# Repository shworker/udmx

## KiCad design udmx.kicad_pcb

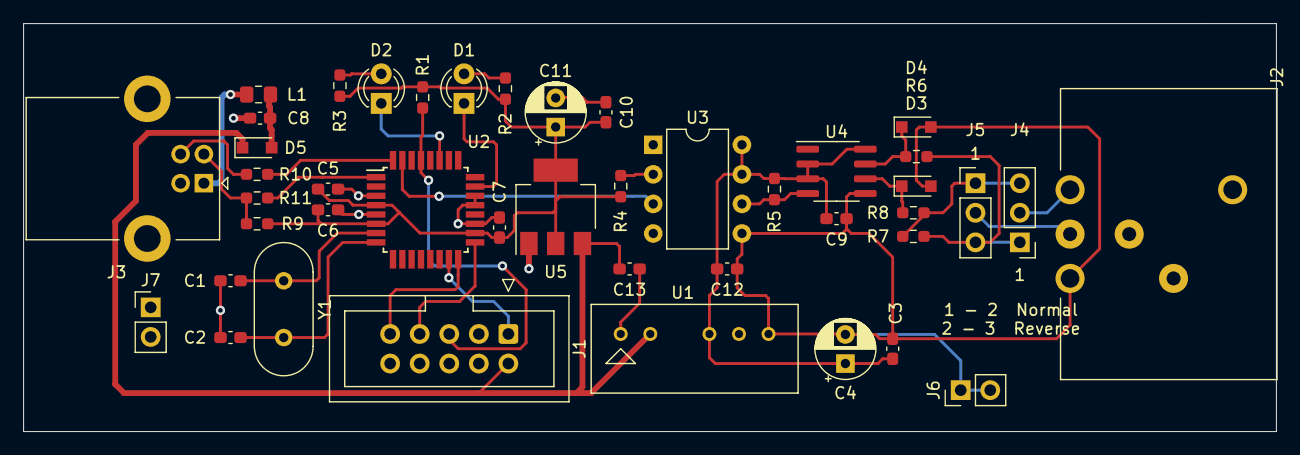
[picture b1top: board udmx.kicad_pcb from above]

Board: 2 copper layers, 107.6 x 35.1 mm, 43 parts (0 on the bottom side), 30 nets.

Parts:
C1, C2: 16pF; C_0603_1608Metric_Pad1.08x0.95mm_HandSolder
C3, C5, C6, C7, C8, C9, C10, C12, C13: 100n; C_0603_1608Metric_Pad1.08x0.95mm_HandSolder
C4, C11: 4.7uF; CP_Radial_D5.0mm_P2.50mm
D1, D2: LED; LED_D3.0mm
D3, D4: BZX384; D_SOD-323_HandSoldering
D5: BAT20J; D_SOD-323_HandSoldering
J1: AVR-ISP-10; IDC-Header_2x05_P2.54mm_Vertical
J2: XLR3; NC3MAH
J3: USB_B; USB_B_Lumberg_2411_02_Horizontal
J4, J5: Conn_01x03_Male; PinHeader_1x03_P2.54mm_Vertical
J6: GND_ISO; PinHeader_1x02_P2.54mm_Vertical
J7: GND; PinHeader_1x02_P2.54mm_Vertical
L1: 600R; L_0805_2012Metric_Pad1.15x1.40mm_HandSolder
R1: 10k; R_0603_1608Metric_Pad0.98x0.95mm_HandSolder
R2, R3: 300R; R_0603_1608Metric_Pad0.98x0.95mm_HandSolder
R4: 100R; R_0603_1608Metric_Pad0.98x0.95mm_HandSolder
R5: 1k; R_0603_1608Metric_Pad0.98x0.95mm_HandSolder
R6, R8: 22R; R_0603_1608Metric_Pad0.98x0.95mm_HandSolder
R7: 120R; R_0603_1608Metric_Pad0.98x0.95mm_HandSolder
R9: 1,5k; R_0603_1608Metric_Pad0.98x0.95mm_HandSolder
R10, R11: 68R; R_0603_1608Metric_Pad0.98x0.95mm_HandSolder
U1: TMR1-0511; SIP-6
U2: ATmega8-16AU; TQFP-32_7x7mm_P0.8mm
U3: 6N137; DIP-8_W7.62mm
U4: MAX485E; SOIC-8_3.9x4.9mm_P1.27mm
U5: LM1117-3.3; SOT-223-3_TabPin2
Y1: 12 MHz; Crystal_HC49-4H_Vertical

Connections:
+3V3: C5.1, C6.1, C7.1, C10.1, C11.1, R1.1, R2.1, R3.1, R4.2, R9.1, U2.4, U2.6, U2.18, U5.2
+5V: C13.1, D5.1, J1.2, U1.2, U5.3
/5VISO+: C3.1, C4.1, C9.1, C12.1, R5.1, U1.4, U3.7, U3.8, U4.2, U4.3, U4.8
/5VISO-: C3.2, C4.2, C9.2, C12.2, D3.2, D4.2, J2.1, J6.1, J6.2, U1.6, U3.5, U4.5
/DATA+: R10.2, U2.32
/DATA-: R11.2, U2.1
/DMXDATA: U2.31, U3.3
/MISO: J1.9, U2.16
/MOSI: J1.1, U2.15
/RESET: J1.5, R1.2, U2.29
/SCK: J1.7, U2.17
/UD+: J3.3, R10.1
/UD-: J3.2, R9.2, R11.1
/VBUS: J3.1, L1.1
GND: C1.2, C2.2, C5.2, C6.2, C7.2, C8.2, C10.2, C11.2, C13.2, J1.4, J1.6, J1.8, J1.10, J3.4, J3.5, J7.1, J7.2, U1.1, U2.3, U2.5, U2.19, U2.21, U2.22, U5.1
unnamed: C1.1, U2.7, Y1.1
unnamed: C2.1, U2.8, Y1.2
unnamed: C8.1, D5.2, L1.2
unnamed: D1.1, U2.23
unnamed: D1.2, R2.2
unnamed: D2.1, U2.27
unnamed: D2.2, R3.2
unnamed: D3.1, R8.2, U4.6
unnamed: D4.1, R6.2, U4.7
unnamed: J2.2, J4.2
unnamed: J2.3, J5.2
unnamed: J4.1, J5.3, R6.1, R7.2
unnamed: J4.3, J5.1, R7.1, R8.1
unnamed: R4.1, U3.2
unnamed: R5.2, U3.6, U4.4
